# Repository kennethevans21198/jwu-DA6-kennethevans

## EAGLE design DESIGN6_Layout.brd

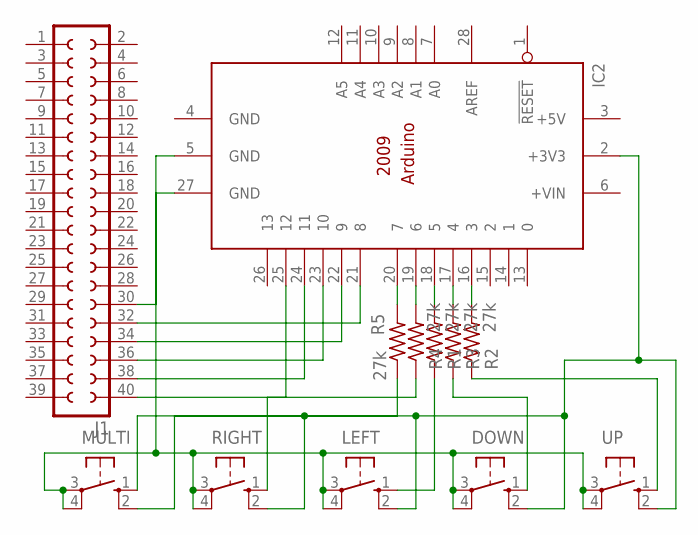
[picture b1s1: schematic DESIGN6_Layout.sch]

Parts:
DOWN: 10-XX; B3F-10XX
IC2: ARDUINO2009_10; ARDUINO2009
J1: SOCKET-40V; S40V
LEFT: 10-XX; B3F-10XX
MULTI: 10-XX; B3F-10XX
R1, R2, R3, R4, R5: 27k; 0204/5
RIGHT: 10-XX; B3F-10XX
UP: 10-XX; B3F-10XX

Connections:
+5V: IC2.3 (+5V)
GND: IC2.4 (GND)
unnamed: IC2.19 (6), R4.2
unnamed: IC2.18 (5), R1.2
unnamed: IC2.25 (12), J1.40
unnamed: IC2.16 (3), R2.2
unnamed: DOWN.2 (S1), IC2.2 (+3V3), LEFT.2 (S1), MULTI.2 (S1), RIGHT.2 (S1), UP.2 (S1)
unnamed: IC2.20 (7), R5.2
unnamed: IC2.17 (4), R3.2
unnamed: IC2.24 (11), J1.38
unnamed: IC2.23 (10), J1.36
unnamed: IC2.22 (9), J1.34
unnamed: IC2.21 (8), J1.32
unnamed: IC2.27 (GND), J1.30
unnamed: DOWN.3, DOWN.4 (P1), IC2.5 (GND), LEFT.3, LEFT.4 (P1), MULTI.3, MULTI.4 (P1), RIGHT.3, RIGHT.4 (P1), UP.3, UP.4 (P1)
unnamed: R2.1, UP.1 (S)
unnamed: DOWN.1 (S), R3.1
unnamed: LEFT.1 (S), R1.1
unnamed: R4.1, RIGHT.1 (S)
unnamed: MULTI.1 (S), R5.1

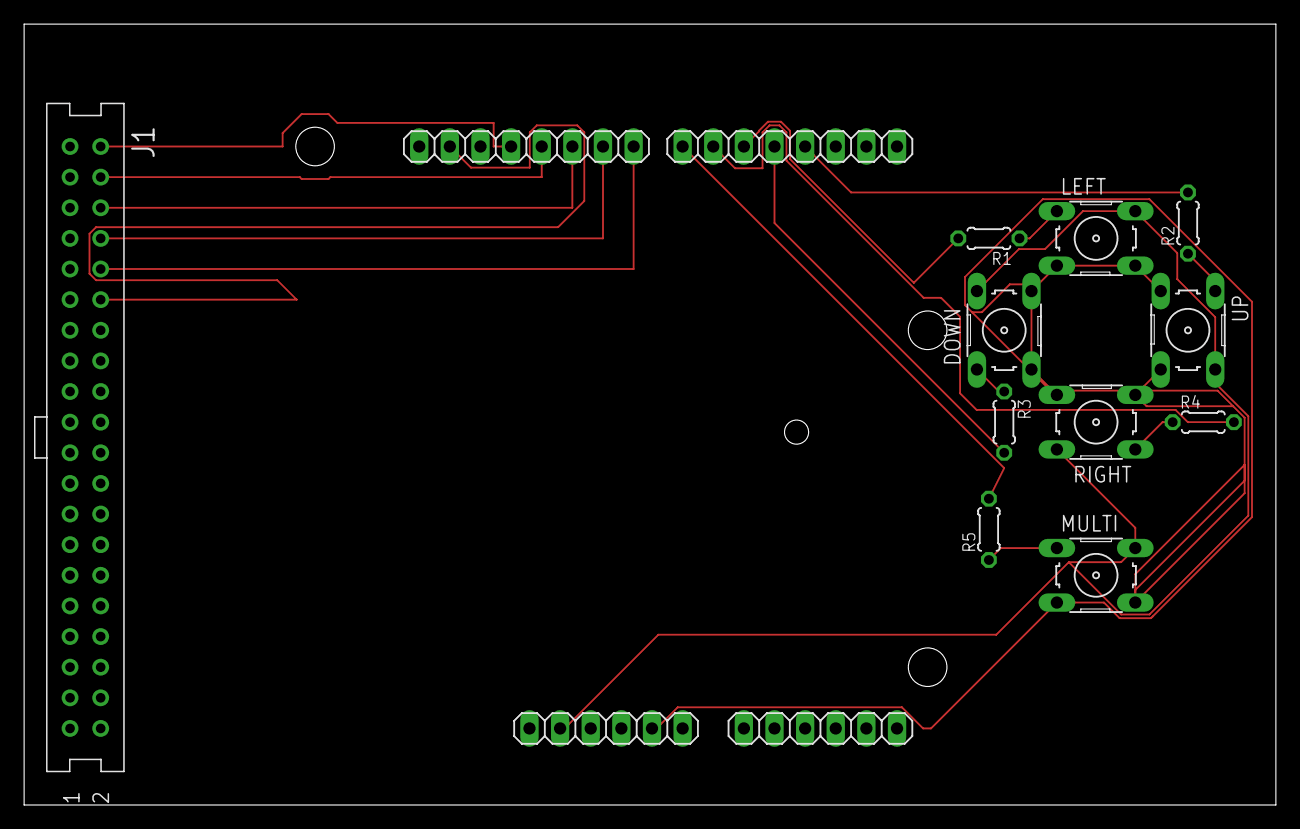
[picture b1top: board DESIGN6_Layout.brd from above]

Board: 2 copper layers, 103.8 x 64.8 mm, 12 parts (0 on the bottom side), 18 nets.
